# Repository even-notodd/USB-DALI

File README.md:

# USB-DALI
USB-DALI adapter. The device works as a gateway allowing sending data via USB VCP (USB Virtual COM Port) to DALI bus and reading data from DALI bus via Modbus RTU protocol. The device can be operated via standard Modbus RTU commands set. Data exchange examples can be found in the repo. Hardware includes DALI bus power supply. Software includes C# sample of sending basic DALI commands including DALI configuration and a simple GUI.

## Hardware
This design has been tested before and successfully used in several systems. 
The device is built around popular STM32F103C8T6 using MCUs USB. The DALI "physical layer" is build with a few discrete components without any special transceiver.
The hardware implementation also includes DALI bus power supply which simplifies its usage in building hardware setups through design & development process. Nevertheless we don't recommend (!) using it as bus power supply in any permanent installations.

The module can work with DALI line powered from external DALI power supply or powered from 
own built-in 16V 160mA converter (powered from USB). If you are planning to use external power supply 
it’s important to open 2 jumpers on the board before connection the module to DALI network and USB. Do 
not use 2 power supplies (external and internal) at the same time! While working with both of jumpers
 open (external power supply), the module provides galvanic isolation between USB and DALI, but when 
powered from built-in power supply, DALI line has not galvanic isolation from USB.
 Being connected to USB, the module can be found in operating system as virtual COM port. It’s 
important to admit, that after connection to that port from the software, it takes MCU some time to create 
stable connection so it’s recommended to keep 3-5 seconds pause between connection and start of data 
exchange.

## Software
The software is a demo GUI providing simple access to direct and indirect commands in DALI network (like broadcasting of brightness, working with individual addresses etc).
Visual Studio Community Edition can be used to build or modify.

## Drivers & settings
The device works as VCP (Virtual COM Port). When using with Linux - no drivers required. For Windows - [VCP driver](https://www.st.com/en/development-tools/stsw-stm32102.html) from ST Microelectronics should be used.
 The Modbus address of the USB-DALI module is 0x01 (not changeable). As far as there is no possibility to connect other devices to the same USB VCP, it will be always the only device in created 
Modbus network.

## Firmware
Firmware file can be found in corresponding sub-folder and can be flashed to MCU with ST-Link (optionally J-Link).

## Protocol
For protocol description and examples look inside  

## License
See the  for details.

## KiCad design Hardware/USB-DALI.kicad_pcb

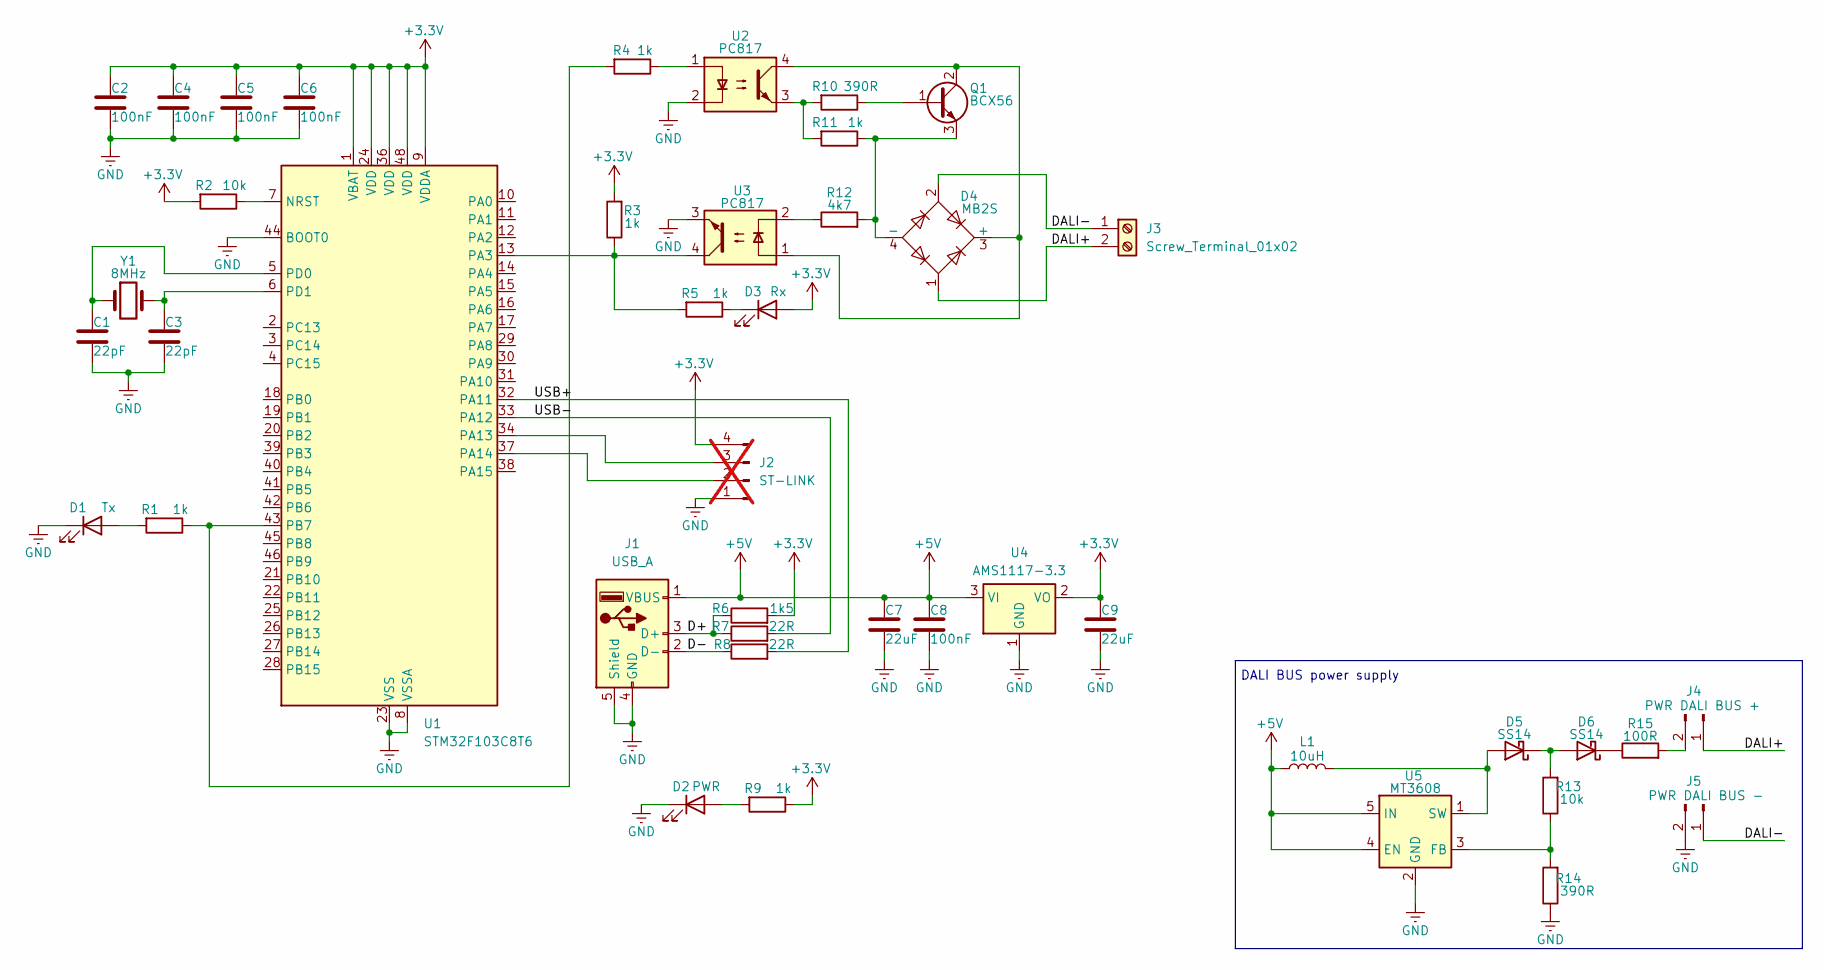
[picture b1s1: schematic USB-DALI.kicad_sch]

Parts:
C1, C3: 22pF; C_0805_2012Metric
C2, C4, C5, C6, C8: 100nF; C_0805_2012Metric
C7, C9: 22uF; C_0805_2012Metric
D1: Tx; LED_0805_2012Metric
D2: PWR; LED_0805_2012Metric
D3: Rx; LED_0805_2012Metric
D4: MB2S; TO-269AA
D5, D6: SS14; D_SMA
J1: USB_A; USB_A_CNCTech_1001-011-01101_Horizontal
J2: ST-LINK; PinHeader_1x04_P2.54mm_Vertical; not fitted
J3: Screw_Terminal_01x02; TerminalBlock_Phoenix_MKDS-1,5-2-5.08_1x02_P5.08mm_Horizont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
J4: PWR DALI BUS +; PinHeader_1x02_P2.54mm_Vertical
J5: PWR DALI BUS -; PinHeader_1x02_P2.54mm_Vertical
L1: 10uH; L_1210_3225Metric
Q1: BCX56; SOT-89-3
R1, R3, R4, R5, R9, R11: 1k; R_0805_2012Metric
R2, R13: 10k; R_0805_2012Metric
R6: 1k5; R_0805_2012Metric
R7, R8: 22R; R_0805_2012Metric
R10, R14: 390R; R_0805_2012Metric
R12: 4k7; R_0805_2012Metric
R15: 100R; R_2512_6332Metric
U1: STM32F103C8T6; LQFP-48_7x7mm_P0.5mm
U2, U3: PC817; DIP-4_W7.62mm
U4: AMS1117-3.3; SOT-223-3_TabPin2
U5: MT3608; SOT-23-6
Y1: 8MHz; Crystal_HC49-U_Vertical

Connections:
+3.3V: C2.1, C4.1, C5.1, C6.1, C9.1, D3.2 (A), J2.4, R2.2, R3.2, R6.2, R9.1, U1.1 (VBAT), U1.9 (VDDA), U1.24 (VDD), U1.36 (VDD), U1.48 (VDD), U4.2 (VO)
+5V: C7.1, C8.1, J1.1 (VBUS), L1.1, U4.3 (VI), U5.4 (EN), U5.5 (IN)
/D+: J1.3 (D+), R6.1, R7.1
/D-: J1.2 (D-), R8.1
/DALI+: D4.1, J3.2, J4.1
/DALI-: D4.2, J3.1, J5.1
/USB+: R8.2, U1.32 (PA11)
/USB-: R7.2, U1.33 (PA12)
GND: C1.2, C2.2, C3.2, C4.2, C5.2, C6.2, C7.2, C8.2, C9.2, D1.1 (K), D2.1 (K), J1.4 (GND), J1.5 (Shield), J2.1, J5.2, R14.1, U1.8 (VSSA), U1.23 (VSS), U1.35 (VSS), U1.44 (BOOT0), U1.47 (VSS), U2.2, U3.3, U4.1 (GND), U5.2 (GND)
unnamed: D1.2 (A), R1.2
unnamed: D2.2 (A), R9.2
unnamed: D3.1 (K), R5.1
unnamed: D4.3 (+), Q1.2 (C), U2.4, U3.1
unnamed: D4.4 (-), Q1.3 (E), R11.1, R12.2
unnamed: D5.2 (A), L1.2, U5.1 (SW)
unnamed: D5.1 (K), D6.2 (A), R13.2
unnamed: D6.1 (K), R15.1
unnamed: J2.2, U1.37 (PA14)
unnamed: J2.3, U1.34 (PA13)
unnamed: J4.2, R15.2
unnamed: Q1.1 (B), R10.1
unnamed: R4.1, U2.1
unnamed: R10.2, R11.2, U2.3
unnamed: R12.1, U3.2
unnamed: R2.1, U1.7 (NRST)
unnamed: R3.1, R5.2, U1.13 (PA3), U3.4
unnamed: R1.1, R4.2, U1.43 (PB7)
unnamed: C1.1, U1.5 (PD0), Y1.1
unnamed: C3.1, U1.6 (PD1), Y1.2
unnamed: R13.1, R14.2, U5.3 (FB)

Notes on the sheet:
DALI BUS power supply

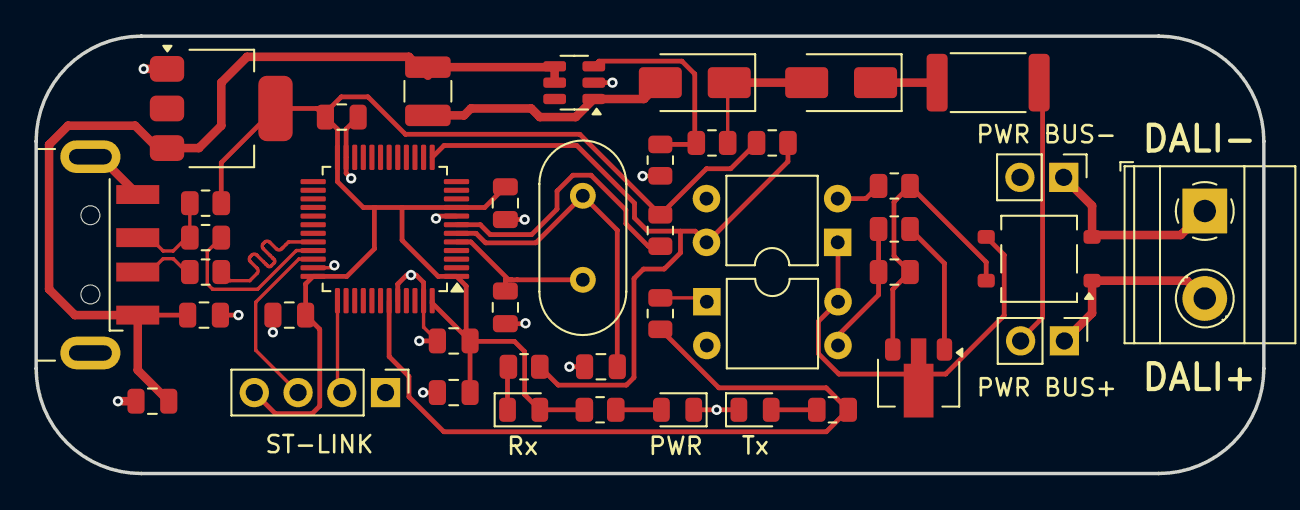
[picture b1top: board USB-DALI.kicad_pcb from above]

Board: 2 copper layers, 71.3 x 25.4 mm, 43 parts (0 on the bottom side), 30 nets.

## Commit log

2025-03-16 Create LICENSE
2025-03-19 Protocol description added
2025-03-23 a silk fix & gerbers
2025-03-23 Readme change and IMG
2025-04-06 Schematics in pdf and link to win driver added
2025-04-06 readme link fix
2025-04-20 C# app added
2025-04-20 gitignore for HW added
2025-06-03 USB connector MPN
2025-06-08 gitignore fix and design added
2025-06-09 HW photo
2026-03-07 Schematics as JPG added
2026-03-24 Update LICENSE

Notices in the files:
README.md:
See the LICENSE file for details.
